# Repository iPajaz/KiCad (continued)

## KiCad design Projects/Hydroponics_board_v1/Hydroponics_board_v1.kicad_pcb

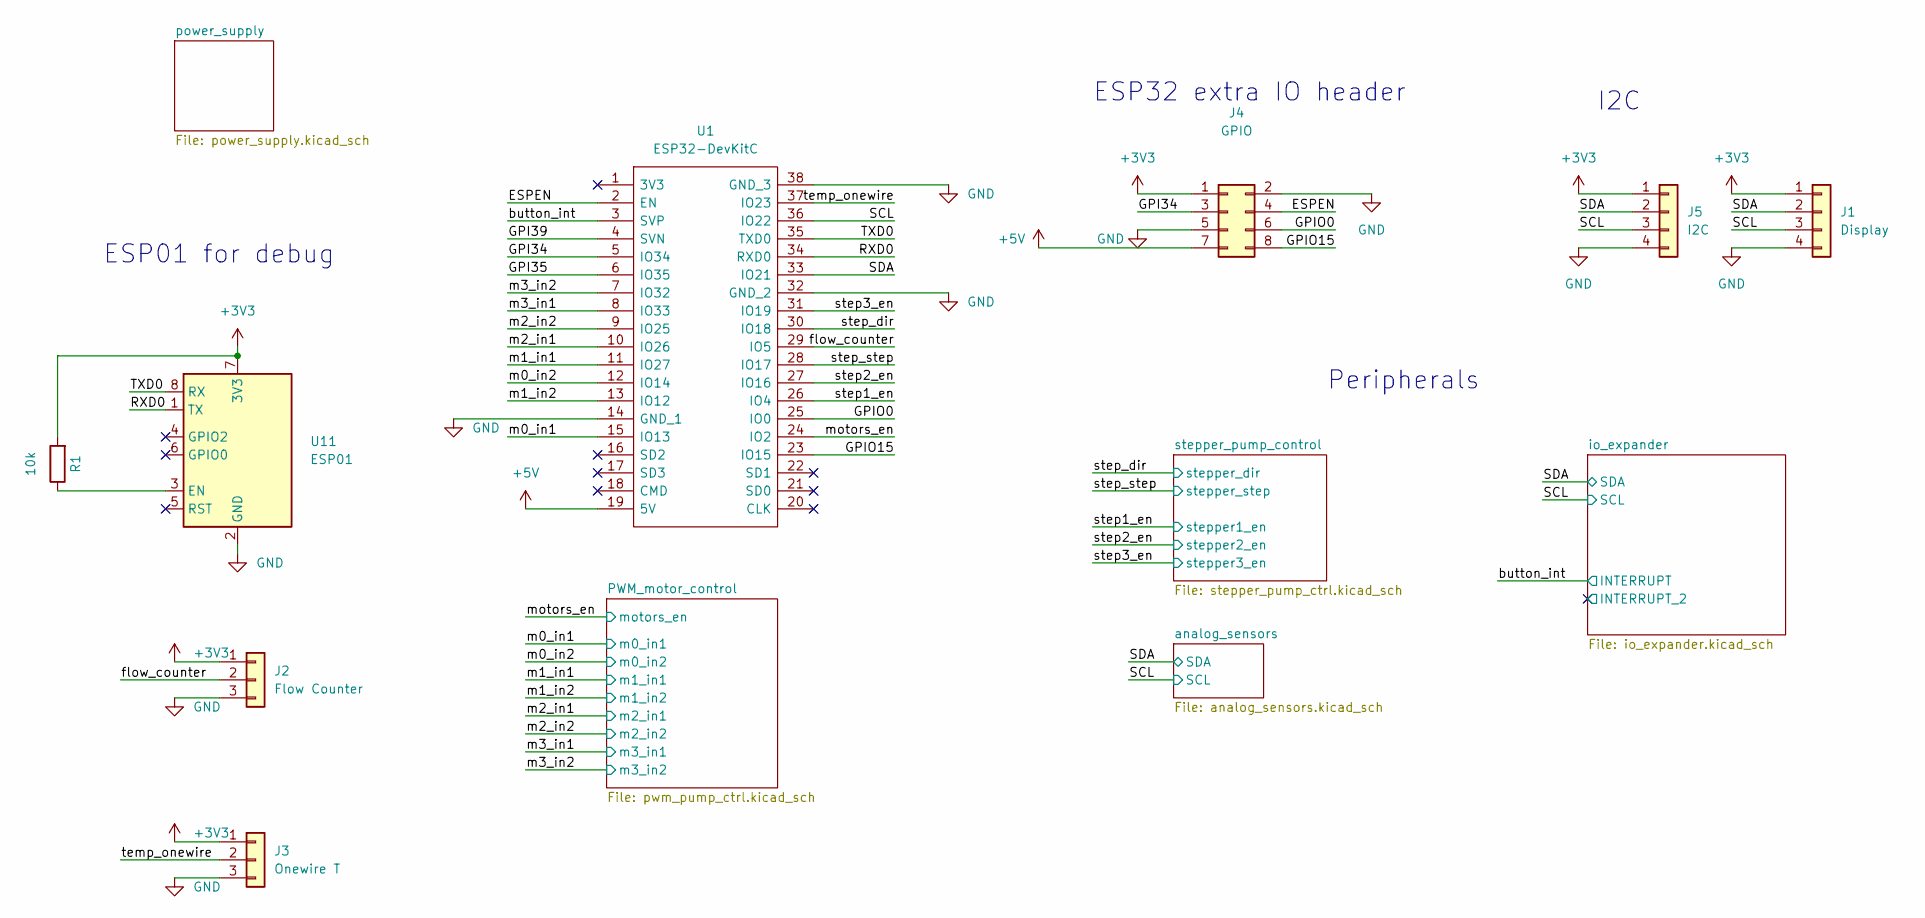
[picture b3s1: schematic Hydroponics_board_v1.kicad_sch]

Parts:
J1: Display; PinHeader_1x04_P2.54mm_Vertical
J2: Flow Counter; PinHeader_1x03_P2.54mm_Vertical
J3: Onewire T; PinHeader_1x03_P2.54mm_Vertical
J4: GPIO; PinHeader_2x04_P2.54mm_Vertical
J5: I2C; PinHeader_1x04_P2.54mm_Vertical
R1: 10k; R_1206_3216Metric
U1: ESP32-DevKitC; ESP32_DevKitC_V4; Manufacturer_Part_Number ESP32-DevKitC
U11: ESP01

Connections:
+5V: J4.7, U1.19 (5V); also elsewhere on the board
/ESPEN: J4.4, U1.2 (EN)
/GPI34: J4.3, U1.5 (IO34)
/GPI35: U1.6 (IO35)
/GPI39: U1.4 (SVN)
/GPIO0: J4.6, U1.25 (IO0)
/GPIO15: J4.8, U1.23 (IO15)
/RXD0: U1.34 (RXD0), U11.1 (TX)
/SCL: J1.3, J5.3, U1.36 (IO22); also elsewhere on the board
/SDA: J1.2, J5.2, U1.33 (IO21); also elsewhere on the board
/TXD0: U1.35 (TXD0), U11.8 (RX)
/button_int: U1.3 (SVP); also elsewhere on the board
/flow_counter: J2.2, U1.29 (IO5)
/m0_in1: U1.15 (IO13); also elsewhere on the board
/m0_in2: U1.12 (IO14); also elsewhere on the board
/m1_in1: U1.13 (IO12); also elsewhere on the board
/m1_in2: U1.11 (IO27); also elsewhere on the board
/m2_in1: U1.10 (IO26); also elsewhere on the board
/m2_in2: U1.9 (IO25); also elsewhere on the board
/m3_in1: U1.7 (IO32); also elsewhere on the board
/m3_in2: U1.8 (IO33); also elsewhere on the board
/motors_en: U1.24 (IO2); also elsewhere on the board
/step1_en: U1.26 (IO4); also elsewhere on the board
/step2_en: U1.27 (IO16); also elsewhere on the board
/step3_en: U1.31 (IO19); also elsewhere on the board
/step_dir: U1.30 (IO18); also elsewhere on the board
/step_step: U1.28 (IO17); also elsewhere on the board
/temp_onewire: J3.2, U1.37 (IO23)
unnamed: R1.1, U11.3 (EN)

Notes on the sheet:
ESP01 for debug
Peripherals
ESP32 extra IO header
I2C

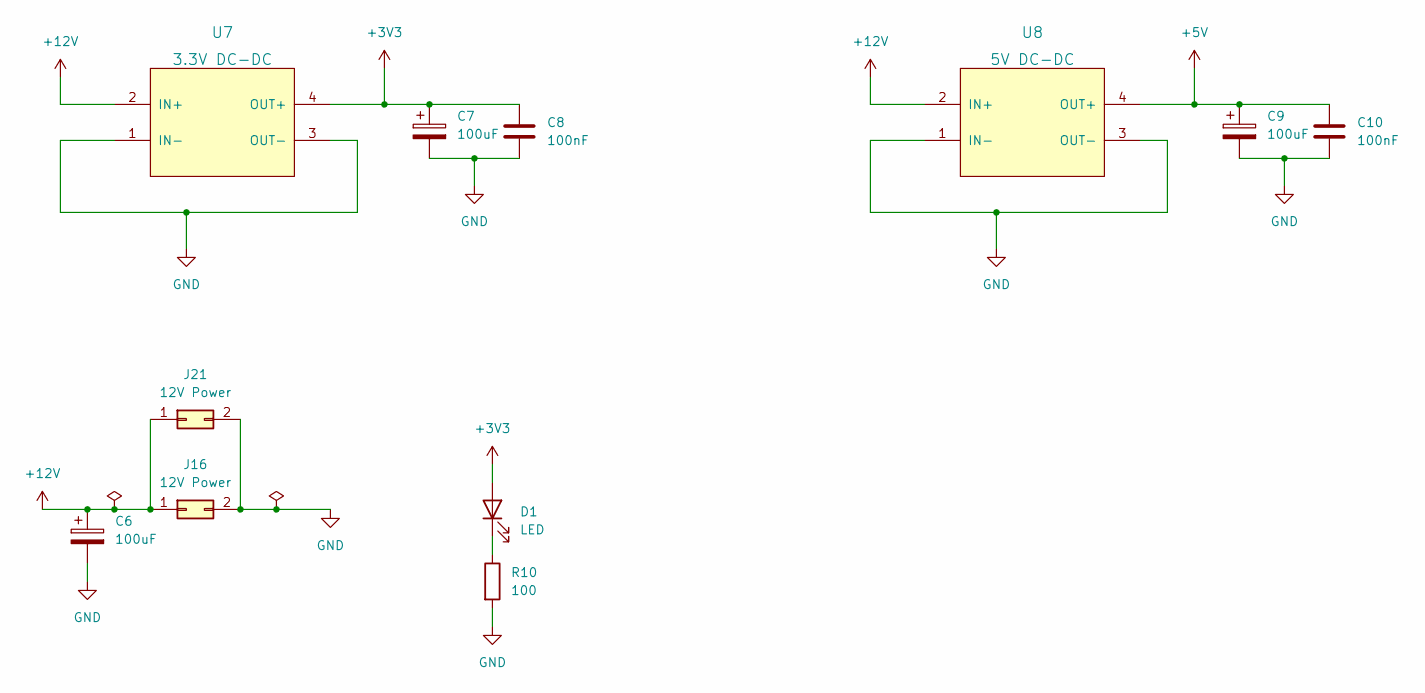
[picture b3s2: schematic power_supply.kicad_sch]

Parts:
C6, C7, C9: 100uF; CP_Radial_Tantal_D7.0mm_P2.50mm
C8, C10: 100nF; C_0805_2012Metric
D1: LED; LED_1206_3216Metric
J16: 12V Power; Molex_Mini-Fit_Jr_5556-02A_2x01_P4.20mm_Vertical
J21: 12V Power; TerminalBlock_Phoenix_MKDS-1,5-2-5.08_1x02_P5.08mm_Horizont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
R10: 100; R_1206_3216Metric
U7: 3.3V DC-DC; Mini360
U8: 5V DC-DC; Mini360

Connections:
+5V: C9.1, C10.1, U8.4 (OUT+); also elsewhere on the board
unnamed: D1.1 (K), R10.1

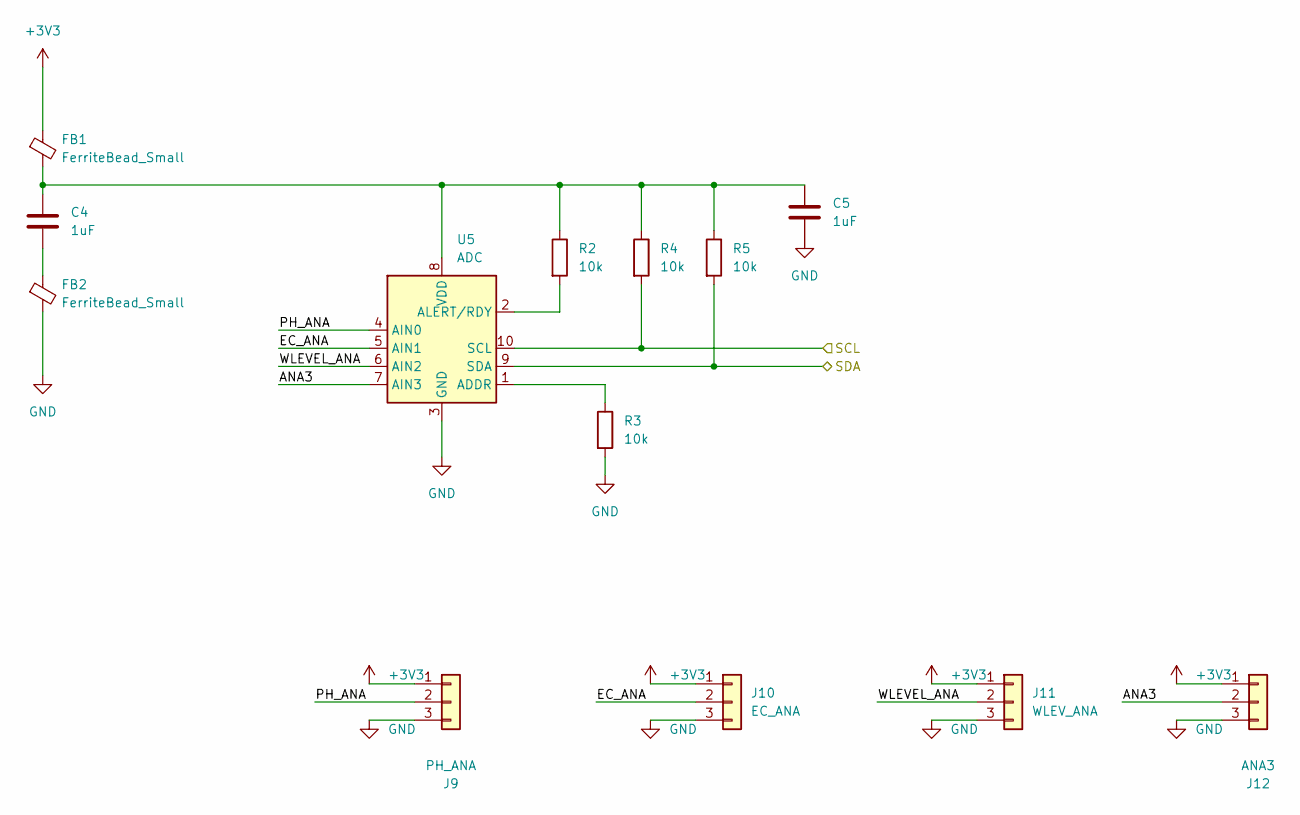
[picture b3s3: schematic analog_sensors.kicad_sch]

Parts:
C4, C5: 1uF; C_0805_2012Metric
FB1, FB2: FerriteBead_Small; R_1206_3216Metric
J9: PH_ANA; PinHeader_1x03_P2.54mm_Vertical
J10: EC_ANA; PinHeader_1x03_P2.54mm_Vertical
J11: WLEV_ANA; PinHeader_1x03_P2.54mm_Vertical
J12: ANA3; PinHeader_1x03_P2.54mm_Vertical
R2, R3, R4, R5: 10k; R_1206_3216Metric
U5: ADC; TSSOP-10_3x3mm_P0.5mm

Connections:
/SCL: R4.2, U5.10 (SCL); also elsewhere on the board
/SDA: R5.2, U5.9 (SDA); also elsewhere on the board
/analog_sensors/ANA3: J12.2, U5.7 (AIN3)
/analog_sensors/EC_ANA: J10.2, U5.5 (AIN1)
/analog_sensors/PH_ANA: J9.2, U5.4 (AIN0)
/analog_sensors/WLEVEL_ANA: J11.2, U5.6 (AIN2)
unnamed: C4.2, FB2.1
unnamed: R2.2, U5.2 (ALERT/RDY)
unnamed: R3.1, U5.1 (ADDR)

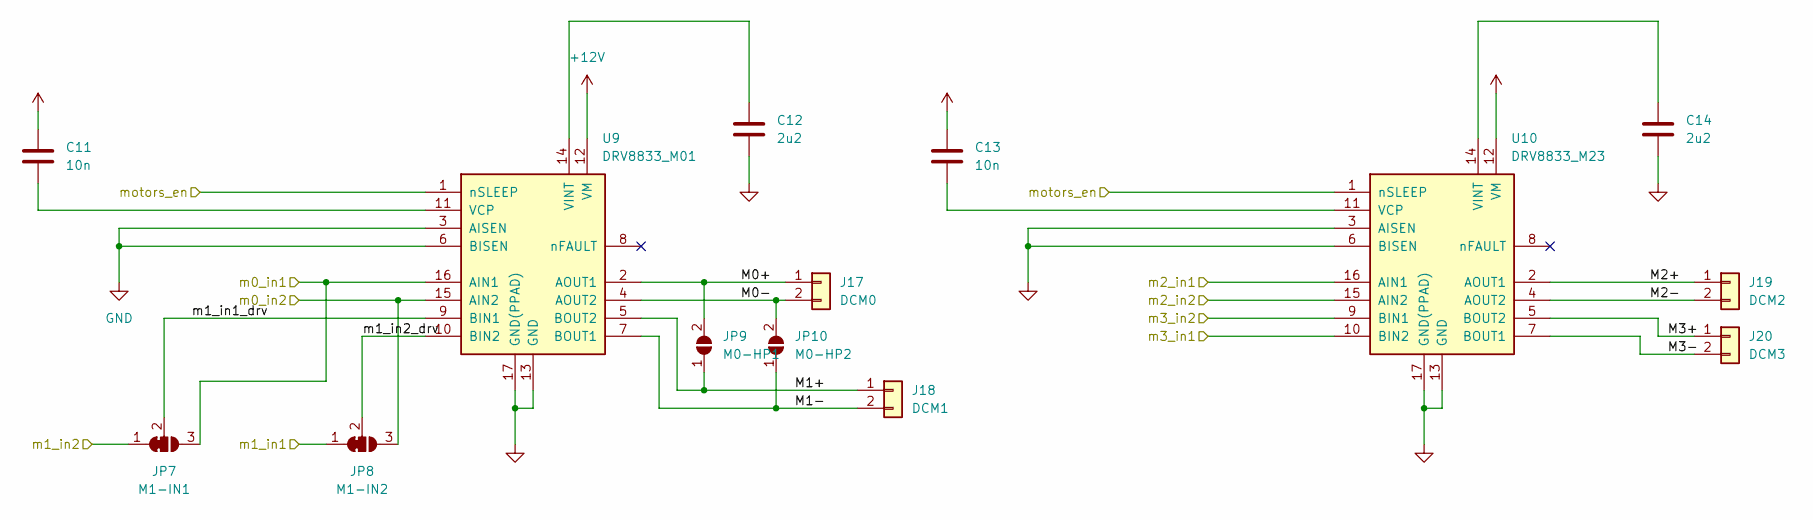
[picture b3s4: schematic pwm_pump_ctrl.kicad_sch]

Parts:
C11, C13: 10n; C_0805_2012Metric
C12, C14: 2u2; C_0805_2012Metric
J17: DCM0; JST_XH_B2B-XH-A_1x02_P2.50mm_Vertical
J18: DCM1; JST_XH_B2B-XH-A_1x02_P2.50mm_Vertical
J19: DCM2; JST_XH_B2B-XH-A_1x02_P2.50mm_Vertical
J20: DCM3; JST_XH_B2B-XH-A_1x02_P2.50mm_Vertical
JP7: M1-IN1; SolderJumper-3_P1.3mm_Open_RoundedPad1.0x1.5mm
JP8: M1-IN2; SolderJumper-3_P1.3mm_Open_RoundedPad1.0x1.5mm
JP9: M0-HP1; SolderJumper-2_P1.3mm_Open_Pad1.0x1.5mm
JP10: M0-HP2; SolderJumper-2_P1.3mm_Open_Pad1.0x1.5mm
U9: DRV8833_M01; HTSSOP-16-DRV8833
U10: DRV8833_M23; HTSSOP-16-DRV8833

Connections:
/PWM_motor_control/M0+: J17.1, JP9.2 (B), U9.2 (AOUT1)
/PWM_motor_control/M0-: J17.2, JP10.2 (B), U9.4 (AOUT2)
/PWM_motor_control/M1+: J18.1, JP9.1 (A), U9.5 (BOUT2)
/PWM_motor_control/M1-: J18.2, JP10.1 (A), U9.7 (BOUT1)
/PWM_motor_control/M2+: J19.1, U10.2 (AOUT1)
/PWM_motor_control/M2-: J19.2, U10.4 (AOUT2)
/PWM_motor_control/M3+: J20.1, U10.5 (BOUT2)
/PWM_motor_control/M3-: J20.2, U10.7 (BOUT1)
/PWM_motor_control/m1_in1_drv: JP7.2 (C), U9.9 (BIN1)
/PWM_motor_control/m1_in2_drv: JP8.2 (C), U9.10 (BIN2)
/m0_in1: JP7.3 (B), U9.16 (AIN1); also elsewhere on the board
/m0_in2: JP8.3 (B), U9.15 (AIN2); also elsewhere on the board
/m1_in1: JP7.1 (A); also elsewhere on the board
/m1_in2: JP8.1 (A); also elsewhere on the board
/m2_in1: U10.16 (AIN1); also elsewhere on the board
/m2_in2: U10.15 (AIN2); also elsewhere on the board
/m3_in1: U10.9 (BIN1); also elsewhere on the board
/m3_in2: U10.10 (BIN2); also elsewhere on the board
/motors_en: U9.1 (nSLEEP), U10.1 (nSLEEP); also elsewhere on the board
unnamed: C11.2, U9.11 (VCP)
unnamed: C12.1, U9.14 (VINT)
unnamed: C13.2, U10.11 (VCP)
unnamed: C14.1, U10.14 (VINT)

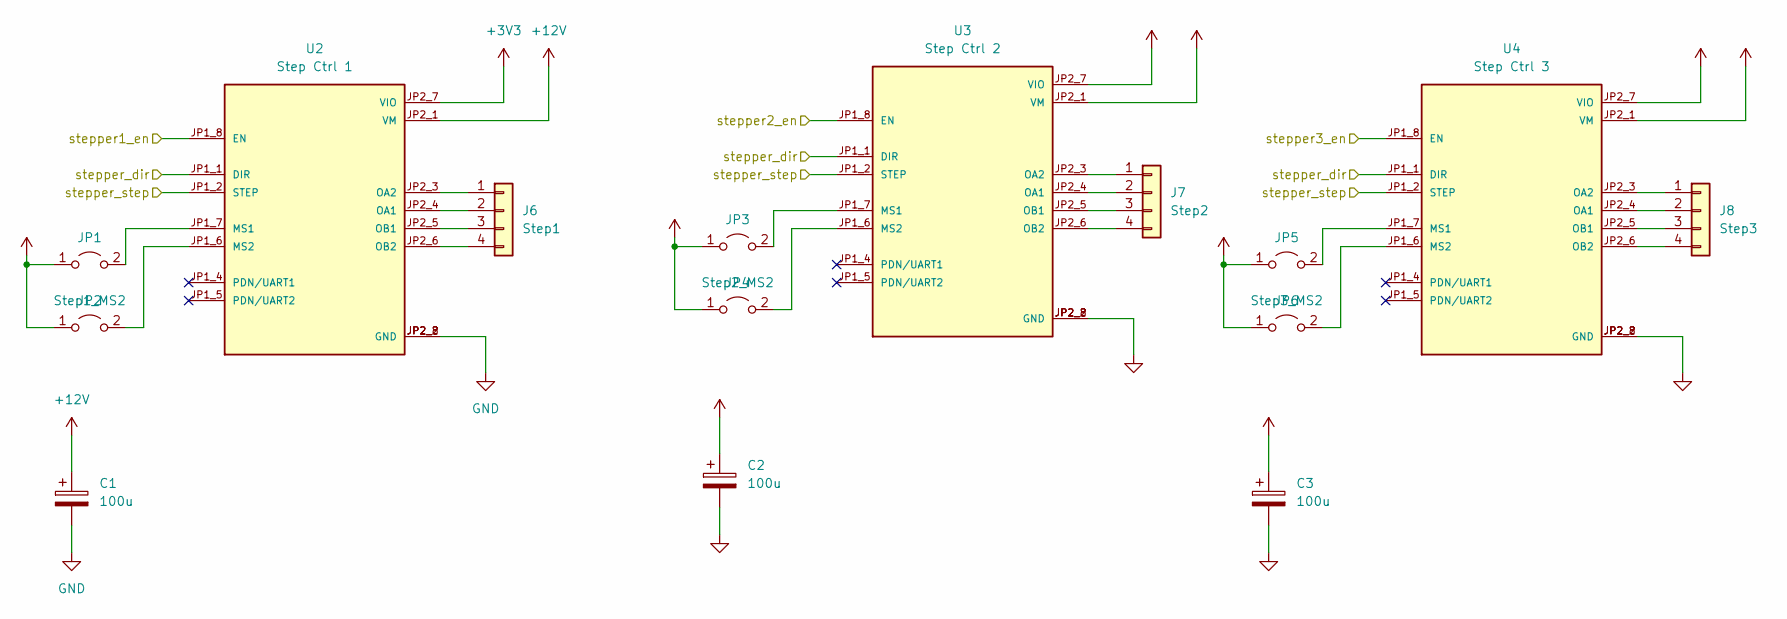
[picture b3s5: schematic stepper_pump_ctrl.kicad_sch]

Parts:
C1, C2, C3: 100u; CP_Horizontal_Tantal_D7.0mm_P2.50mm_Flip
J6: Step1; PinHeader_1x04_P2.54mm_Vertical
J7: Step2; PinHeader_1x04_P2.54mm_Vertical
J8: Step3; PinHeader_1x04_P2.54mm_Vertical
JP1: Step1_MS1; PinHeader_1x02_P2.54mm_Vertical
JP2: Step1_MS2; PinHeader_1x02_P2.54mm_Vertical
JP3: Step2_MS1; PinHeader_1x02_P2.54mm_Vertical
JP4: Step2_MS2; PinHeader_1x02_P2.54mm_Vertical
JP5: Step3_MS1; PinHeader_1x02_P2.54mm_Vertical
JP6: Step3_MS2; PinHeader_1x02_P2.54mm_Vertical
U2: Step Ctrl 1; TMC2208_Module
U3: Step Ctrl 2; TMC2208_Module
U4: Step Ctrl 3; TMC2208_Module

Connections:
/step1_en: U2.JP1_8 (EN); also elsewhere on the board
/step2_en: U3.JP1_8 (EN); also elsewhere on the board
/step3_en: U4.JP1_8 (EN); also elsewhere on the board
/step_dir: U2.JP1_1 (DIR), U3.JP1_1 (DIR), U4.JP1_1 (DIR); also elsewhere on the board
/step_step: U2.JP1_2 (STEP), U3.JP1_2 (STEP), U4.JP1_2 (STEP); also elsewhere on the board
unnamed: J6.1, U2.JP2_3 (OA2)
unnamed: J6.2, U2.JP2_4 (OA1)
unnamed: J6.3, U2.JP2_5 (OB1)
unnamed: J6.4, U2.JP2_6 (OB2)
unnamed: J7.1, U3.JP2_3 (OA2)
unnamed: J7.2, U3.JP2_4 (OA1)
unnamed: J7.3, U3.JP2_5 (OB1)
unnamed: J7.4, U3.JP2_6 (OB2)
unnamed: J8.1, U4.JP2_3 (OA2)
unnamed: J8.2, U4.JP2_4 (OA1)
unnamed: J8.3, U4.JP2_5 (OB1)
unnamed: J8.4, U4.JP2_6 (OB2)
unnamed: JP1.2 (B), U2.JP1_7 (MS1)
unnamed: JP2.2 (B), U2.JP1_6 (MS2)
unnamed: JP3.2 (B), U3.JP1_7 (MS1)
unnamed: JP4.2 (B), U3.JP1_6 (MS2)
unnamed: JP5.2 (B), U4.JP1_7 (MS1)
unnamed: JP6.2 (B), U4.JP1_6 (MS2)

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
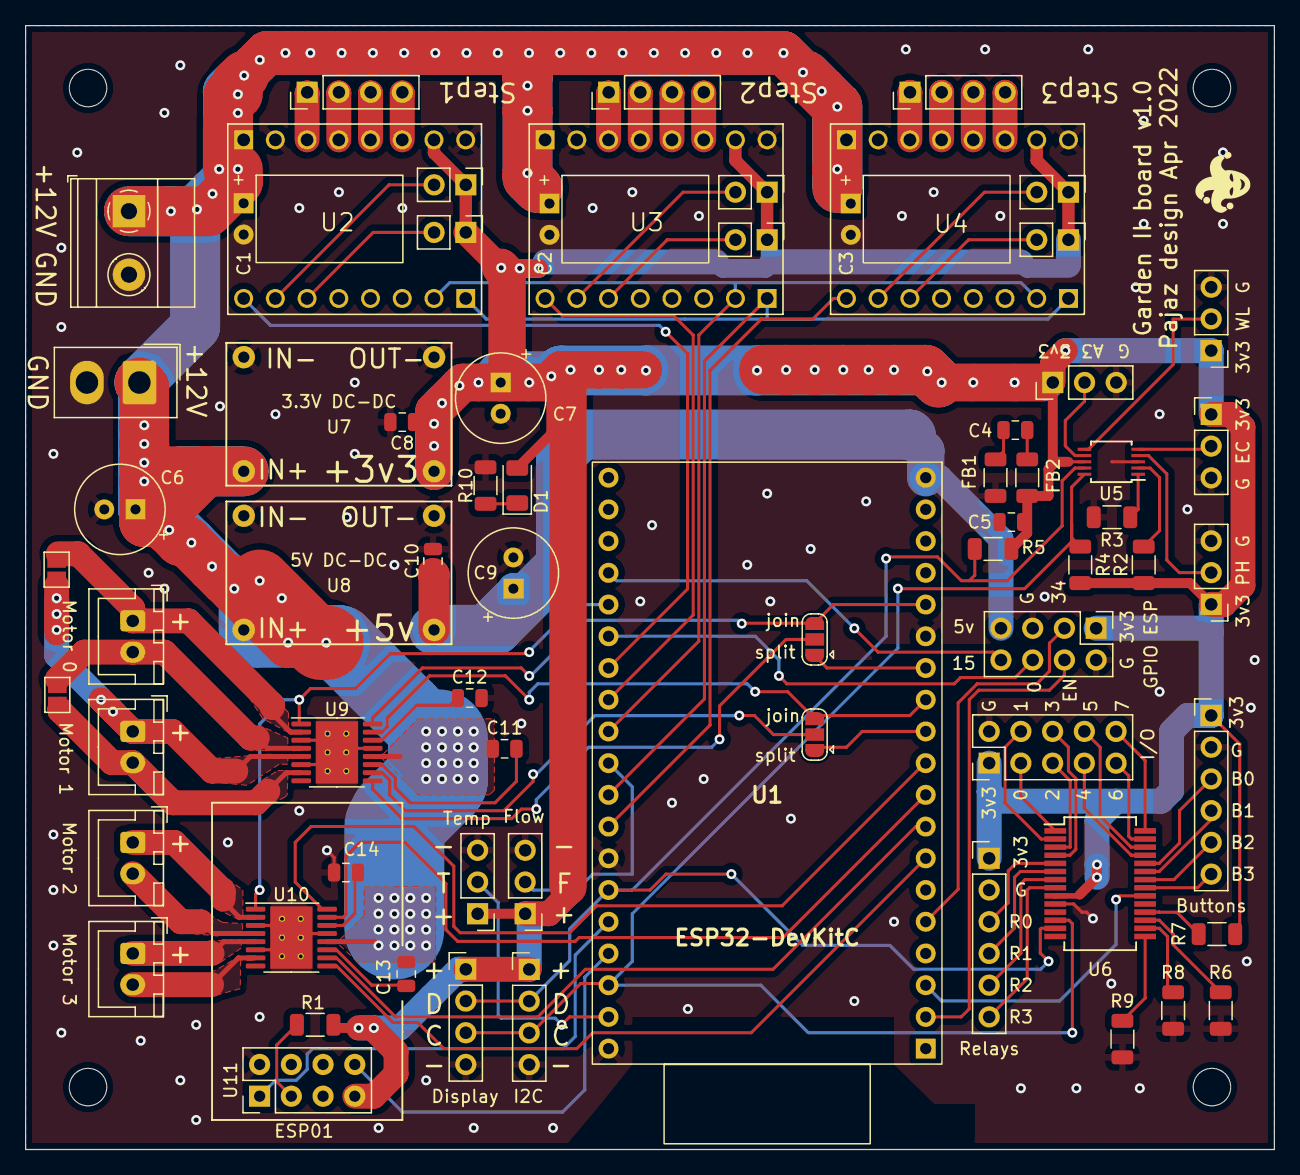
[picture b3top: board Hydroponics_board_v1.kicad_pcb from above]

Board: 2 copper layers, 100.0 x 90.0 mm, 73 parts (0 on the bottom side), 91 nets.

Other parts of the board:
J13: IO; PinHeader_2x05_P2.54mm_Vertical
J14: Relays; PinHeader_1x06_P2.54mm_Vertical
J15: Buttons; PinHeader_1x06_P2.54mm_Vertical
MH3, MH3#2, MH3#3, MH3#4: MountingHole_3mm
R6, R7, R8, R9: 10k; R_1206_3216Metric
U6: MCP23017; SSOP-28_5.3x10.2mm_P0.65mm

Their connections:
/SCL: U6.12 (SCK); also elsewhere on the board
/SDA: U6.13 (SDA); also elsewhere on the board
/button_int: U6.20 (INTA); also elsewhere on the board
/io_expander/BUTTON0: J15.3, U6.24 (GPA3)
/io_expander/BUTTON1: J15.4, U6.23 (GPA2)
/io_expander/BUTTON2: J15.5, U6.22 (GPA1)
/io_expander/BUTTON3: J15.6, U6.21 (GPA0)
/io_expander/IO0: J13.3, U6.1 (GPB0)
/io_expander/IO1: J13.4, U6.2 (GPB1)
/io_expander/IO2: J13.5, U6.3 (GPB2)
/io_expander/IO3: J13.6, U6.4 (GPB3)
/io_expander/IO4: J13.7, U6.25 (GPA4)
/io_expander/IO5: J13.8, U6.26 (GPA5)
/io_expander/IO6: J13.9, U6.27 (GPA6)
/io_expander/IO7: J13.10, U6.28 (GPA7)
/io_expander/RELAY0: J14.3, U6.5 (GPB4)
/io_expander/RELAY1: J14.4, U6.6 (GPB5)
/io_expander/RELAY2: J14.5, U6.7 (GPB6)
/io_expander/RELAY3: J14.6, U6.8 (GPB7)
unnamed: R6.2, U6.17 (A2)
unnamed: R7.2, U6.18 (~RESET)
unnamed: R8.2, U6.16 (A1)
unnamed: R9.2, U6.15 (A0)

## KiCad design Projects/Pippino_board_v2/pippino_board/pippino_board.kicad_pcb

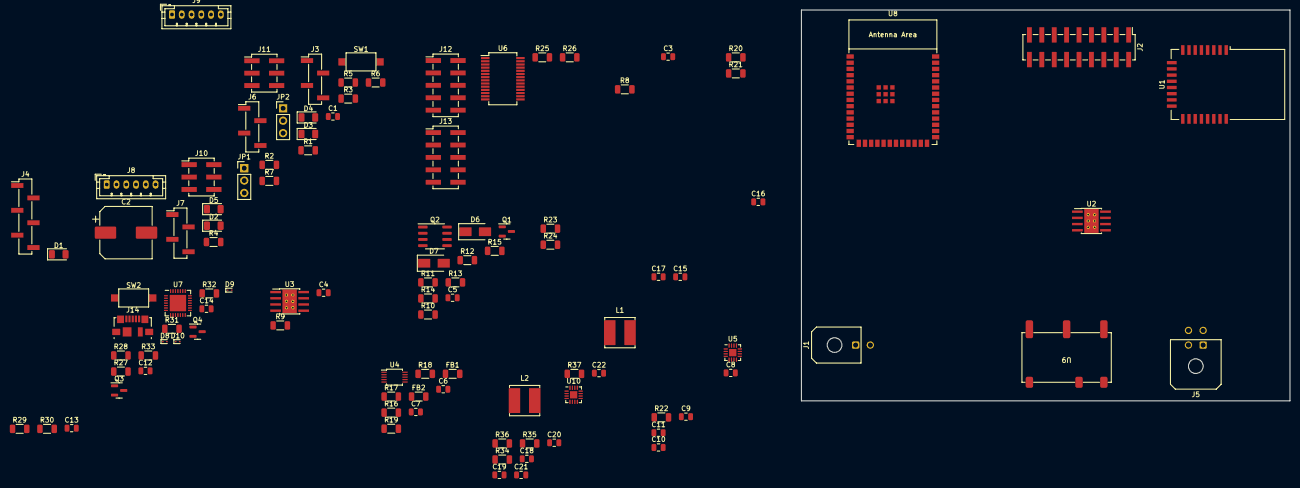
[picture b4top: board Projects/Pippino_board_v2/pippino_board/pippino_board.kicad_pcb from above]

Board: 2 copper layers, 100.0 x 80.0 mm, 106 parts (0 on the bottom side), 106 nets, no tracks yet.

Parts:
C1, C5, C8, C12, C15, C18: 10uF; C_0805_2012Metric
C2: 470uF; CP_Elec_10x10.5
C3, C4: 0.1uF; C_0805_2012Metric
C6, C7, C13, C14, C16: 1uF; C_0805_2012Metric
C9, C19: 1u; C_0805_2012Metric
C10, C20: 10p; C_0805_2012Metric
C11, C21: 22u; C_0805_2012Metric
C17, C22: 100n; C_0805_2012Metric
D1, D2, D3, D4, D5: LED; LED_1206_3216Metric
D6, D7: 1N5819; D_SMA
D8, D9, D10: ESD9B5.0ST5G; D_SOD-923
FB1, FB2: FerriteBead_Small; R_1206_3216Metric
J1: Conn_02x01; Molex_Micro-Fit_3.0_43045-0200_2x01_P3.00mm_Horizontal
J2: Conn_02x09_Odd_Even; PinHeader_2x09_P2.54mm_Vertical_SMD
J3, J6, J7: Conn_01x04; PinHeader_1x04_P2.54mm_Vertical_SMD_Pin1Left
J4: Conn_01x06; PinHeader_1x06_P2.54mm_Vertical_SMD_Pin1Left
J5: Conn_02x02_Counter_Clockwise; Molex_Micro-Fit_3.0_43045-0400_2x02_P3.00mm_Horizontal
J8, J9: Conn_01x06; JST_PH_B6B-PH-K_1x06_P2.00mm_Vertical
J10, J11: Conn_02x03; PinHeader_2x03_P2.54mm_Vertical_SMD
J12, J13: IO; PinHeader_2x05_P2.54mm_Vertical_SMD
J14: USB_B_Micro; USB_Micro-B_Molex_47346-0001
JP1, JP2: Jumper_3_Open; PinHeader_1x03_P2.54mm_Vertical
L1, L2: 6.8u 2A; L_Bourns_SRN6045TA
MH3: MountingHole_3mm
Q1: 2N3904; SOT-23
Q2: AO4409; SOIC-8_3.9x4.9mm_P1.27mm
Q3, Q4: L8050_SOT23; SOT-23
R1, R2, R3, R4, R5: 330; R_1206_3216Metric
R6, R8, R9: 18k; R_1206_3216Metric
R7: 5.1k; R_1206_3216Metric
R10, R15: 220K; R_1206_3216Metric
R11, R14: 220; R_1206_3216Metric
R12, R35: 100K; R_1206_3216Metric
R13: 100k; R_1206_3216Metric
R16, R17, R18, R19, R25, R26: 10k; R_1206_3216Metric
R20, R23: 560K; R_1206_3216Metric
R21, R24: 300K; R_1206_3216Metric
R22, R36, R37: 1M; R_1206_3216Metric
R27: 22.1K; R_1206_3216Metric
R28: 47.5K; R_1206_3216Metric
R29: 1K; R_1206_3216Metric
R30, R31: 10K(NC); R_1206_3216Metric
R32, R33: 10K; R_1206_3216Metric
R34: 720K; R_1206_3216Metric
SW1, SW2: SW_Push; SW_SPST_CK_RS282G05A3
U1: E18-MS1-PCB
U2, U3: DRV8871DDA; Texas_HTSOP-8-1EP_3.9x4.9mm_P1.27mm_EP2.95x4.9mm_Mask2.4x3.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
U4: ADS1115IDGS; TSSOP-10_3x3mm_P0.5mm
U5, U10: TPS62110; HVQFN-16-1EP_3x3mm_P0.5mm_EP1.5x1.5mm
U6: MCP23017; SSOP-28_5.3x10.2mm_P0.65mm
U7: CP2102N-Axx-xQFN28; QFN-28-1EP_5x5mm_P0.5mm_EP3.35x3.35mm
U8: ESP32-S3-WROOM-1
U9: CKCS_BK03; CKCS-BK03

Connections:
3V3_GATED: C7.1, C10.1, C11.1, C12.1, FB1.1, J8.5, J9.5, L1.2, R16.1, R18.1, R19.1, R22.1, R29.1, R31.2, U4.8 (VDD), U7.6 (VDD), U7.7 (VREGIN), U8.2 (3V3)
5V0_GATED: C15.1, C16.1, C17.1, D5.2 (A), J5.3, U9.3 (Vout)
+3V3: C1.1, C20.1, C21.1, C22.1, J2.1, J3.1, J4.1, J6.1, J7.1, J12.1, J13.1, L2.2, R25.1, R36.1, R37.1, SW1.1, U1.2 (VDD), U6.9 (VDD)
+BATT: C2.1, C18.1, C19.1, J1.2, R12.1, R20.1, R34.1, U10.2 (VIN), U10.3 (VIN), U10.4 (EN), U10.8 (VINA)
/ADC/ADS_IN1: R6.2, R7.1, U4.5 (AIN1)
/ADS0: J2.6, U4.4 (AIN0)
/ADS2: J2.8, U4.6 (AIN2)
/ADS3: J2.10, U4.7 (AIN3)
/Batt_Low_Flag: J2.18, R34.2, R35.1, R37.2, U1.6 (P1.7), U8.23 (GPIO21), U10.6 (LBO), U10.7 (LBI)
/E18DC: J2.16, U1.3 (P2.2)
/E18DD: J2.14, U1.4 (P2.1)
/E18P10: JP2.3 (B), U1.15 (P1.0)
/E18P14: J2.5, U1.11 (P1.4)
/E18P15: J2.7, U1.10 (P1.5)
/E18P16: J2.9, JP1.1 (A), U1.7 (P1.6)
/E18RST: J2.12, U1.24 (~RESET)
/E18RX: J2.11, U1.21 (P0.2), U8.18 (GPIO10/TOUCH10/ADC1_CH9/FSPICS0/FSPIIO4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)
/E18TX: J2.13, U1.20 (P0.3), U8.17 (GPIO9/TOUCH9/ADC1_CH8/FSPIHD/SUBSPIHD)
/ESP32_Module/DTR: Q4.2 (E), R32.2, U7.28 (~DTR)
/ESP32_Module/GPIO0: Q4.3 (C), U8.27 (GPIO0/BOOT)
/ESP32_Module/RTS: Q3.2 (E), R33.2, U7.24 (~RTS)
/ESP32_Module/USB_DN: D9.1 (A1), J14.3 (D+), U7.5 (D-)
/ESP32_Module/USB_DP: D10.1 (A1), J14.2 (D-), U7.4 (D+)
/ESP32_Module/VBUS: D8.1 (A1), J14.1 (VBUS), R27.1
/ESPEN: C14.1, J2.4, Q3.3 (C), R31.1, SW2.1, U8.3 (EN)
/ESPIO1: J2.15, U8.39 (GPIO1/TOUCH1/ADC1_CH0)
/ESPIO2: J2.17, U8.38 (GPIO2/TOUCH2/ADC1_CH1)
/ESPIO11: J3.2, U8.19 (GPIO11/TOUCH11/ADC2_CH0/FSPID/FSPIIO5/S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)
/ESPIO12: J3.3, U8.20 (GPIO12/TOUCH12/ADC2_CH1/FSPICLK/FSPIIO6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)
/ESPIO13: J6.2, U8.21 (GPIO13/TOUCH13/ADC2_CH2/FSPIQ/FSPIIO7/S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)
/ESPIO14: J6.3, U8.22 (GPIO14/TOUCH14/ADC2_CH3/FSPIWP/FSPIDQS/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)
/ESPIO19: D3.2 (A), U8.13 (GPIO19/U1RTS/ADC2_CH8/CLK_OUT2/USB_D-)
/ESPIO20: D4.2 (A), U8.14 (GPIO20/U1CTS/ADC2_CH9/CLK_OUT1/USB_D+)
/ESPIO35: JP1.3 (B), U8.28 (SPIIO6/GPIO35/FSPID/SUBSPID)
/EXT1: J2.3, JP2.1 (A)
/M1+: J8.1, U2.6 (OUT1)
/M1-: J8.6, U2.8 (OUT2)
/M1PWM1: J10.4, U2.3 (IN1), U8.11 (GPIO18/U1RXD/ADC2_CH7/CLK_OUT3)
/M1PWM2_brake: J10.6, U2.2 (IN2), U8.12 (GPIO8/TOUCH8/ADC1_CH7/SUBSPICS1)
/M1enc1: J8.4, J10.2, U8.8 (GPIO15/U0RTS/ADC2_CH4/XTAL_32K_P)
/M1enc2_dir: J8.3, J10.5, U8.7 (GPIO7/TOUCH7/ADC1_CH6)
/M2+: J9.1, U3.6 (OUT1)
/M2-: J9.6, U3.8 (OUT2)
/M2PWM1: J11.4, U3.3 (IN1), U8.9 (GPIO16/U0CTS/ADC2_CH5/XTAL_32K_NH5)
/M2PWM2_brake: J11.6, U3.2 (IN2), U8.10 (GPIO17/U1TXD/ADC2_CH6)
/M2enc1: J9.4, J11.2, U8.6 (GPIO6/TOUCH6/ADC1_CH5)
/M2enc2_dir: J9.3, J11.5, U8.5 (GPIO5/TOUCH5/ADC1_CH4)
/MISO: J4.3, U8.34 (MTDI/GPIO41/CLK_OUT1)
/MOSI: J4.2, U8.35 (MTMS/GPIO42)
/PSU_3v3_BATT/TPS62110_MODULE_BATT/FB_1v15: C20.2, R20.2, R21.1, U10.10 (FB)
/PSU_Gated/PSU_3v3/TPS62110_MODULE/FB_1v15: C10.2, R23.2, R24.1, U5.10 (FB)
/RXD0: U7.26 (TXD), U8.36 (U0RXD/GPIO44/CLK_OUT2)
/SCL: J7.3, U8.31 (GPIO38/FSPIWP/SUBSPIWP)
/SCL_INT: R18.2, U4.10 (SCL), U6.12 (SCK), U8.25 (GPIO48/SPICLK_N/SUBSPICLK_N_DIFF)
/SDA: J7.2, U8.30 (SPIDQS/GPIO37/FSPIQ/SUBSPIQ)
/SDA_INT: R19.2, U4.9 (SDA), U6.13 (SDA), U8.24 (GPIO47/SPICLK_P/SUBSPICLK_P_DIFF)
/SPICLK: J4.4, U8.33 (MTDO/GPIO40/CLK_OUT2)
/SPICS: J4.5, U8.32 (MTCK/GPIO39/CLK_OUT3/SUBSPICS1)
/TXD0: U7.25 (RXD), U8.37 (U0TXD/GPIO43/CLK_OUT1)
/VBATT_maintain: JP1.2 (C), R14.2, R15.1
/VBATT_trig_manual: D6.1 (K), D7.1 (K), Q1.2 (B), R13.1, SW1.2
/VBATT_trigger: JP2.2 (C), R10.1, R11.1
/button_int: U6.20 (INTA), U8.29 (SPIIO7/GPIO36/FSPICLK/SUBSPICLK)
/io_expander/GPA0: J12.3, U6.21 (GPA0)
/io_expander/GPA1: J12.5, U6.22 (GPA1)
/io_expander/GPA2: J12.7, U6.23 (GPA2)
/io_expander/GPA3: J12.9, U6.24 (GPA3)
/io_expander/GPA4: J12.4, U6.25 (GPA4)
/io_expander/GPA5: J12.6, U6.26 (GPA5)
/io_expander/GPA6: J12.8, U6.27 (GPA6)
/io_expander/GPA7: J12.10, U6.28 (GPA7)
/io_expander/GPB0: J13.3, U6.1 (GPB0)
/io_expander/GPB1: J13.5, U6.2 (GPB1)
/io_expander/GPB2: J13.7, U6.3 (GPB2)
/io_expander/GPB3: J13.9, U6.4 (GPB3)
/io_expander/GPB4: J13.4, U6.5 (GPB4)
/io_expander/GPB5: J13.6, U6.6 (GPB5)
/io_expander/GPB6: J13.8, U6.7 (GPB6)
/io_expander/GPB7: J13.10, U6.8 (GPB7)
GND: C1.2, C2.2, C3.2, C4.2, C5.2, C7.2, C8.2, C9.2, C11.2, C12.2, C13.2, C14.2, C15.2, C16.2, C17.2, C18.2, C19.2, C21.2, C22.2, D8.2 (A2), D9.2 (A2), D10.2 (A2), FB2.2, J1.1, J2.2, J3.4, J4.6, J5.1, J5.2, J6.4, J7.4, J8.2, J9.2, J10.1, J11.1, J12.2, J13.2, J14.5 (GND), J14.6 (Shield), Q1.1 (E), R1.2, R2.2, R3.2, R4.2, R5.2, R7.2, R8.2, R9.2, R10.2, R13.2, R15.2, R17.2, R21.2, R24.2, R26.1, R28.1, R30.1, R35.2, SW2.2, U1.1 (GND), U2.1 (GND), U2.7 (GND), U2.9 (GND), U3.1 (GND), U3.7 (GND), U3.9 (GND), U4.3 (GND), U5.1 (PGND), U5.5 (SYNC), U5.7 (LBI), U5.9 (AGND), U5.11 (GND), U5.12 (GND), U5.16 (PGND), U6.10 (VSS), U7.3 (GND), U7.29 (GND), U8.1 (GND), U8.40 (GND), U8.41 (GND), U9.2 (GND), U10.1 (PGND), U10.5 (SYNC), U10.9 (AGND), U10.11 (GND), U10.12 (GND), U10.16 (PGND)
unnamed: C6.1, FB1.2
unnamed: C6.2, FB2.1
unnamed: C13.1, R27.2, R28.2, U7.8 (VBUS)
unnamed: D1.1 (K), R1.1
unnamed: D2.1 (K), R2.1
unnamed: D3.1 (K), R3.1
unnamed: D4.1 (K), R4.1
unnamed: D5.1 (K), R5.1
unnamed: D6.2 (A), R11.2
unnamed: D7.2 (A), R14.1
unnamed: L1.1, U5.14 (SW), U5.15 (SW)
unnamed: L2.1, U10.14 (SW), U10.15 (SW)
unnamed: Q1.3 (C), Q2.4 (G), R12.2
unnamed: Q3.1 (B), R32.1
unnamed: Q4.1 (B), R33.1
unnamed: R8.1, U2.4 (ILIM)
unnamed: R9.1, U3.4 (ILIM)
unnamed: R16.2, U4.2 (ALERT/RDY)
unnamed: R17.1, U4.1 (ADDR)
unnamed: R22.2, U5.13 (PG)
unnamed: R25.2, U6.18 (~RESET)
unnamed: R26.2, U6.15 (A0), U6.16 (A1), U6.17 (A2)
unnamed: R29.2, U7.9 (~RST)
unnamed: R30.2, U7.11 (~SUSPEND)
unnamed: R36.2, U10.13 (PG)
VBATT_GATED: C3.1, C4.1, C5.1, C8.1, C9.1, J5.4, J10.3, J11.3, R6.1, R23.1, U2.5 (VM), U3.5 (VM), U5.2 (VIN), U5.3 (VIN), U5.4 (EN), U5.8 (VINA), U9.1 (Vin)

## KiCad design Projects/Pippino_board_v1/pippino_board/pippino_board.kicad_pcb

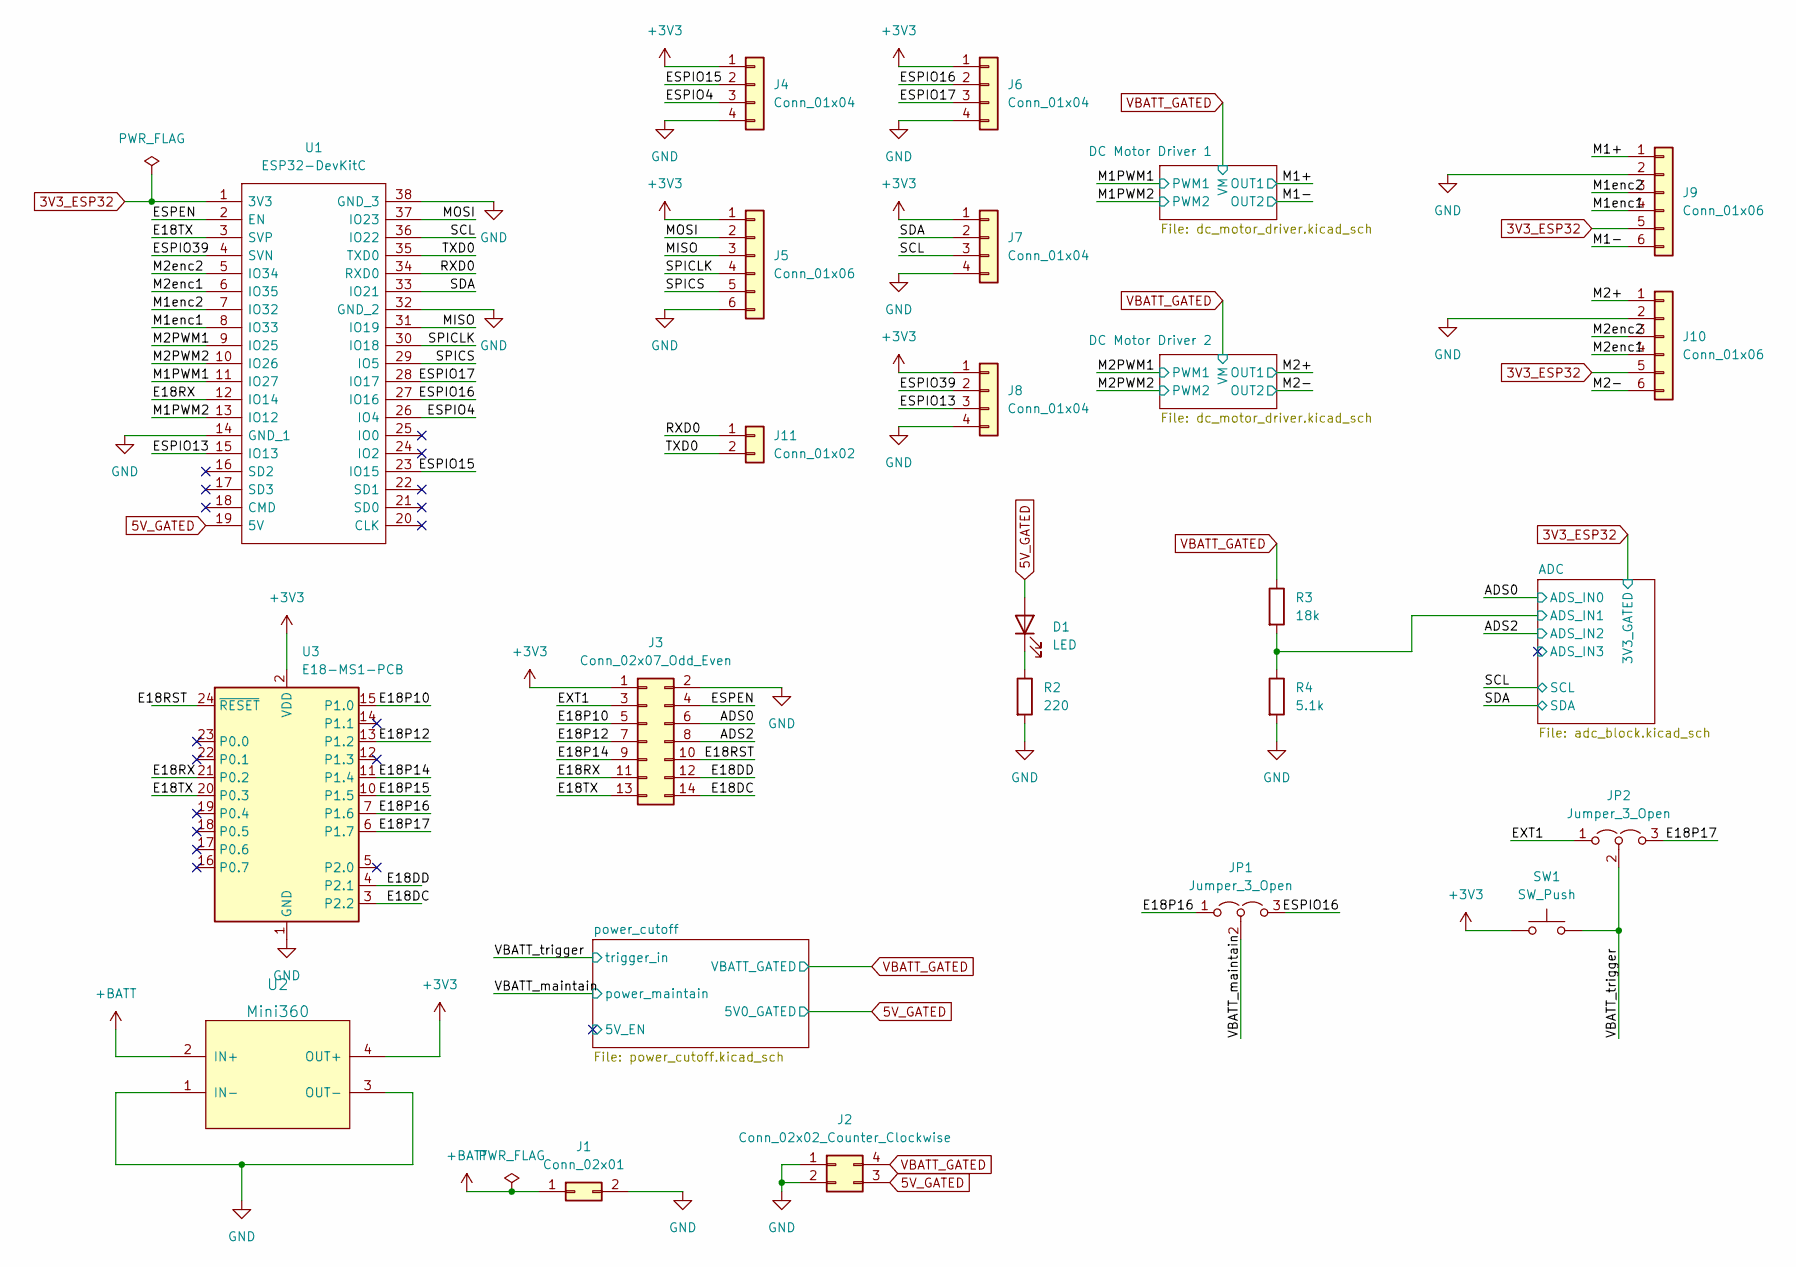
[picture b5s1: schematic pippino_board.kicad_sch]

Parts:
D1: LED; LED_1206_3216Metric
J1: Conn_02x01; Molex_Micro-Fit_3.0_43045-0200_2x01_P3.00mm_Horizontal
J2: Conn_02x02_Counter_Clockwise; Molex_Micro-Fit_3.0_43045-0400_2x02_P3.00mm_Horizontal
J3: Conn_02x07_Odd_Even; PinHeader_2x07_P2.54mm_Vertical
J4, J6, J7, J8: Conn_01x04; PinHeader_1x04_P2.54mm_Vertical
J5: Conn_01x06; PinHeader_1x06_P2.54mm_Vertical
J9, J10: Conn_01x06; JST_PH_B6B-PH-K_1x06_P2.00mm_Vertical
J11: Conn_01x02; PinHeader_1x02_P2.54mm_Horizontal
JP1, JP2: Jumper_3_Open; PinHeader_1x03_P2.54mm_Vertical
R2: 220; R_1206_3216Metric
R3: 18k; R_1206_3216Metric
R4: 5.1k; R_1206_3216Metric
SW1: SW_Push; SW_SPST_CK_RS282G05A3
U1: ESP32-DevKitC; DIP2600W100P254L5400H500Q38N; Manufacturer_Part_Number ESP32-DevKitC
U2: Mini360
U3: E18-MS1-PCB

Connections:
3V3_ESP32: J9.5, J10.5, U1.1 (3V3); also elsewhere on the board
5V_GATED: D1.2 (A), J2.3, U1.19 (5V); also elsewhere on the board
+3V3: J3.1, J4.1, J5.1, J6.1, J7.1, J8.1, SW1.1, U2.4 (OUT+), U3.2 (VDD)
+BATT: J1.1, U2.2 (IN+); also elsewhere on the board
/ADC/ADS_IN1: R3.2, R4.1; also elsewhere on the board
/ADS0: J3.6; also elsewhere on the board
/ADS2: J3.8; also elsewhere on the board
/E18DC: J3.14, U3.3 (P2.2)
/E18DD: J3.12, U3.4 (P2.1)
/E18P10: J3.5, U3.15 (P1.0)
/E18P12: J3.7, U3.13 (P1.2)
/E18P14: J3.9, U3.11 (P1.4)
/E18P15: U3.10 (P1.5)
/E18P16: JP1.1 (A), U3.7 (P1.6)
/E18P17: JP2.3 (B), U3.6 (P1.7)
/E18RST: J3.10, U3.24 (~RESET)
/E18RX: J3.11, U1.12 (IO14), U3.21 (P0.2)
/E18TX: J3.13, U1.3 (SVP), U3.20 (P0.3)
/ESPEN: J3.4, U1.2 (EN)
/ESPIO4: J4.3, U1.26 (IO4)
/ESPIO13: J8.3, U1.15 (IO13)
/ESPIO15: J4.2, U1.23 (IO15)
/ESPIO16: J6.2, JP1.3 (B), U1.27 (IO16)
/ESPIO17: J6.3, U1.28 (IO17)
/ESPIO39: J8.2, U1.4 (SVN)
/EXT1: J3.3, JP2.1 (A)
/M1+: J9.1; also elsewhere on the board
/M1-: J9.6; also elsewhere on the board
/M1PWM1: U1.11 (IO27); also elsewhere on the board
/M1PWM2: U1.13 (IO12); also elsewhere on the board
/M1enc1: J9.4, U1.8 (IO33)
/M1enc2: J9.3, U1.7 (IO32)
/M2+: J10.1; also elsewhere on the board
/M2-: J10.6; also elsewhere on the board
/M2PWM1: U1.9 (IO25); also elsewhere on the board
/M2PWM2: U1.10 (IO26); also elsewhere on the board
/M2enc1: J10.4, U1.6 (IO35)
/M2enc2: J10.3, U1.5 (IO34)
/MISO: J5.3, U1.31 (IO19)
/MOSI: J5.2, U1.37 (IO23)
/RXD0: J11.1, U1.34 (RXD0)
/SCL: J7.3, U1.36 (IO22); also elsewhere on the board
/SDA: J7.2, U1.33 (IO21); also elsewhere on the board
/SPICLK: J5.4, U1.30 (IO18)
/SPICS: J5.5, U1.29 (IO5)
/TXD0: J11.2, U1.35 (TXD0)
/VBATT_maintain: JP1.2 (C); also elsewhere on the board
/VBATT_trigger: JP2.2 (C), SW1.2; also elsewhere on the board
GND: J1.2, J2.1, J2.2, J3.2, J4.4, J5.6, J6.4, J7.4, J8.4, J9.2, J10.2, R2.2, R4.2, U1.14 (GND_1), U1.32 (GND_2), U1.38 (GND_3), U2.1 (IN-), U2.3 (OUT-), U3.1 (GND); also elsewhere on the board
unnamed: D1.1 (K), R2.1
VBATT_GATED: J2.4, R3.1; also elsewhere on the board
